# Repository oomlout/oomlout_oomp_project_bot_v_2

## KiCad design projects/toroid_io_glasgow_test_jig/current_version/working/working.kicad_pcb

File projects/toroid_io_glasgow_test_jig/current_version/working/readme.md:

# glasgow
 
## summary 
* id: toroid_io_glasgow_test_jig
* user: toroid_io
* name: glasgow
* board: test_jig
* repo: https://github.com/Toroid-io/glasgow
* src_file_repo_kicad_pcb: hardware/boards/test-jig/test-jig.kicad_pcb
* src_file_repo_kicad_pcb_link: https://github.com/Toroid-io/glasgow/tree/master/hardware/boards/test-jig/test-jig.kicad_pcb

* src_file_repo_sch: hardware/boards/glasgow.sch
* src_file_repo_sch_link: https://github.com/Toroid-io/glasgow/tree/master/hardware/boards/glasgow.sch
* full details link: https://github.com/oomlout/oomlout_oomp_project_bot_v_2/tree/main/projects/toroid_io_glasgow_test_jig/current_version/working

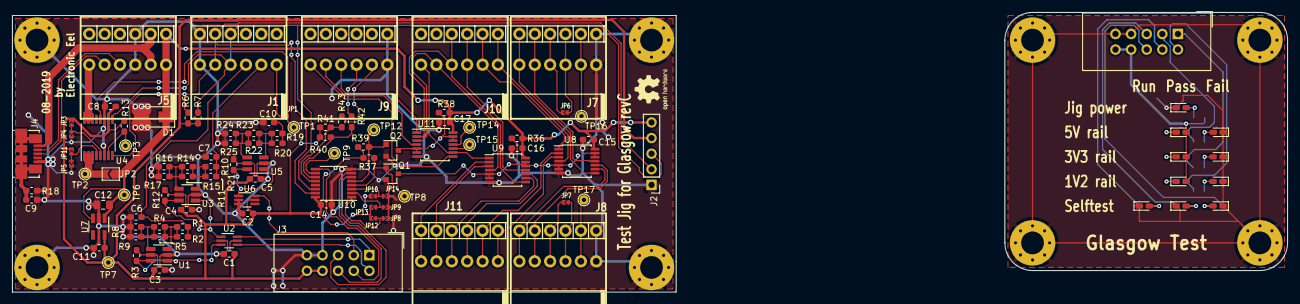
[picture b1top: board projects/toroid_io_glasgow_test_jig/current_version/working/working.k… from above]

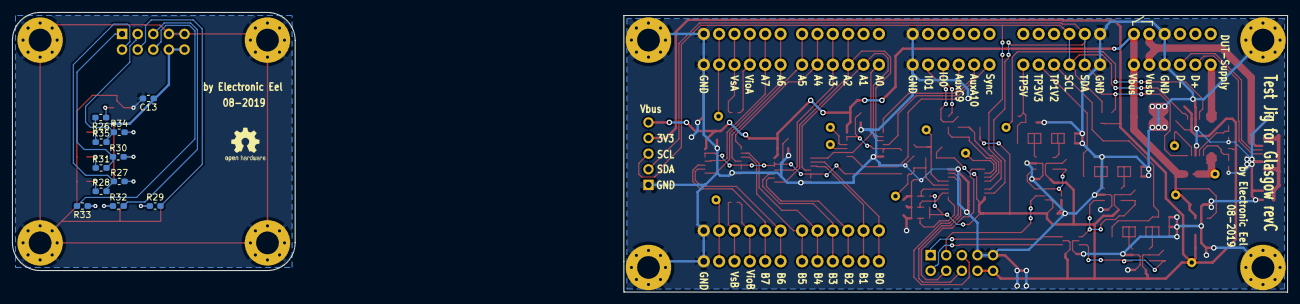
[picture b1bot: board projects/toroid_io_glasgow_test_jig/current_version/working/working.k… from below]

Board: 2 copper layers, 207.5 x 45.5 mm, 129 parts (11 on the bottom side), 90 nets.

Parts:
C1, C2, C3, C4, C5, C6, C7, C8, C9, C10, C13, C14, C15, C16, C17: 100nF; C_0603_1608Metric_Pad1.05x0.95mm_HandSolder
C11: 1µF; C_0603_1608Metric_Pad1.05x0.95mm_HandSolder
C12: 4.7µF; C_0805_2012Metric_Pad1.15x1.40mm_HandSolder
D1: SMAJ5A; D_SMA
D2, D3, D6, D8, D10: green; LED_0603_1608Metric_Castellated
D4, D7, D9, D11: red; LED_0603_1608Metric_Castellated
D5: yellow; LED_0603_1608Metric_Castellated
H1, H2, H3, H4, H5, H6, H7, H8: MountingHole_Pad; MountingHole_3.7mm_Pad_Via
J1, J5, J7, J8, J9, J10, J11: AST04106; TerminalBlock_MetzConnect_AST04106_1x06_Lever_Clamp_45Degree
J2: DNP; PinHeader_1x05_P2.54mm_Vertical
J3, J6: Conn_02x05_Odd_Even; IDC-Header_2x05_P2.54mm_Vertical
J4: USB_B_Micro; USB_Micro-B_Molex_47346-0001
JP1, JP4, JP5, JP6, JP7, JP8, JP9, JP10: SolderJumper_2_Bridged; Solderbridge-small-2pad
JP2: SolderJumper_2_Bridged; SolderJumper-2_P1.3mm_Open_TrianglePad1.0x1.5mm
JP3, JP11, JP12, JP13, JP14: SolderJumper_2_Open; Solderbridge-small-2pad
Q1, Q2: BSS138; SOT-23
R1: 5M1; R_0603_1608Metric_Pad1.05x0.95mm_HandSolder
R2: 68k; R_0603_1608Metric_Pad1.05x0.95mm_HandSolder
R3, R12, R13, R21: 4k7; R_0603_1608Metric_Pad1.05x0.95mm_HandSolder
R4, R8, R16, R22, R24, R40, R41, R42, R43: DNP; R_0603_1608Metric_Pad1.05x0.95mm_HandSolder
R5: 910R; R_0603_1608Metric_Pad1.05x0.95mm_HandSolder
R6, R7: 22k; R_0603_1608Metric_Pad1.05x0.95mm_HandSolder
R9: 33k; R_0603_1608Metric_Pad1.05x0.95mm_HandSolder
R10: 91k; R_0603_1608Metric_Pad1.05x0.95mm_HandSolder
R11: 3M6; R_0603_1608Metric_Pad1.05x0.95mm_HandSolder
R14: 1k; R_0603_1608Metric_Pad1.05x0.95mm_HandSolder
R15: 470R; R_0603_1608Metric_Pad1.05x0.95mm_HandSolder
R17: 12k; R_0603_1608Metric_Pad1.05x0.95mm_HandSolder
R18: 1M; R_0603_1608Metric_Pad1.05x0.95mm_HandSolder
R19: 510k; R_0603_1608Metric_Pad1.05x0.95mm_HandSolder
R20: 110k; R_0603_1608Metric_Pad1.05x0.95mm_HandSolder
R23: 680; R_0603_1608Metric_Pad1.05x0.95mm_HandSolder
R25: 7k5; R_0603_1608Metric_Pad1.05x0.95mm_HandSolder
R26, R27, R28, R29, R30, R31, R32, R33, R34, R35, R36, R38: 2k2; R_0603_1608Metric_Pad1.05x0.95mm_HandSolder
R37, R39: 100K; R_0603_1608Metric_Pad1.05x0.95mm_HandSolder
TP1, TP2, TP3, TP6, TP7, TP8, TP9, TP12, TP14, TP15, TP16, TP17: TestPoint; TestPoint_THTPad_D1.5mm_Drill0.7mm
U1, U3, U5: TPS3700; SOT-23-6_Handsoldering
U2, U6: 74LVC2G14; SOT-363_SC-70-6_Handsoldering
U4: INA260; TSSOP-16_4.4x5mm_P0.65mm
U7: AP2127K-3.3; SOT-23-5_HandSoldering
U8, U9, U11: 74HC4066; TSSOP-14_4.4x5mm_P0.65mm
U10: TCA9534; TSSOP-16_4.4x5mm_P0.65mm

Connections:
+3.3VA: C13.1, D3.2, D6.2, D10.2, J6.8, J6.10, R26.2
+3V3: C1.1, C2.1, C3.1, C4.1, C5.1, C8.1, C11.1, C14.1, J2.4, J3.8, J3.10, JP3.2, JP10.2, JP11.2, JP12.2, JP13.2, R3.1, R6.1, R7.1, R12.1, R13.1, R21.1, R37.1, R39.1, R40.2, R41.2, TP7.1, U1.5, U2.5, U3.5, U4.10, U5.5, U6.5, U7.5, U10.16
/DUT_Supply: J5.6, U4.14, U4.15, U4.16
/LED_1V2: J3.2, U2.4
/LED_3V3: J3.1, U2.6
/LED_5V: J3.3, U6.6
/LED_FAIL: J3.6, U10.7
/LED_PASS: J3.5, U10.6
/LED_RUN: J3.4, U10.9
/SCL: J1.4, J2.3, R7.2, U4.9, U10.14
/SDA: J1.5, J2.2, R6.2, U4.8, U10.15
/TP_1V2: C6.1, J1.3, R1.1, R2.1
/TP_3V3: C7.1, J1.2, R10.1, R11.1
/TP_5V: C10.1, J1.1, JP1.1, R19.1, R20.1
/led-board/LED_1V2: J6.2, R27.1, R28.2
/led-board/LED_3V3: J6.1, R30.1, R31.2
/led-board/LED_5V: J6.3, R34.1, R35.2
/led-board/LED_FAIL: J6.6, R33.2
/led-board/LED_PASS: J6.5, R32.2
/led-board/LED_RUN: J6.4, R29.2
/port-connection/Aux_conn_ctrl_5V: Q2.3, R38.2, U11.5, U11.6, U11.12, U11.13
/port-connection/JIG_GPIO0: J9.3, R42.2
/port-connection/JIG_GPIO1: J9.2, R43.2
/port-connection/Port_conn_ctrl_5V: Q1.3, R36.2, U8.5, U8.6, U8.12, U8.13, U9.5, U9.6, U9.12, U9.13
/port-connection/TP_A0: J10.6, U9.1, U11.9
/port-connection/TP_A1: J10.5, U9.4, U11.3
/port-connection/TP_A2: J10.4, U9.8, U11.2
/port-connection/TP_A3: J10.3, U9.11
/port-connection/TP_A4: J10.2, U8.1
/port-connection/TP_A5: J10.1, U8.4
/port-connection/TP_A6: J7.6, U8.8
/port-connection/TP_A7: J7.5, U8.11
/port-connection/TP_A_Vio: J7.4, JP6.2
/port-connection/TP_A_Vsns: J7.3, JP6.1
/port-connection/TP_Aux_A10: J9.5, U11.4
/port-connection/TP_Aux_C9: J9.4, U11.1
/port-connection/TP_B0: J11.6, U9.2
/port-connection/TP_B1: J11.5, U9.3
/port-connection/TP_B2: J11.4, U9.9
/port-connection/TP_B3: J11.3, U9.10
/port-connection/TP_B4: J11.2, U8.2
/port-connection/TP_B5: J11.1, U8.3
/port-connection/TP_B6: J8.6, U8.9
/port-connection/TP_B7: J8.5, U8.10
/port-connection/TP_B_Vio: J8.4, JP7.2
/port-connection/TP_B_Vsns: J8.3, JP7.1
/port-connection/TP_Sync: J9.6, U11.8
/port-connection/~Aux_conn_ctrl: Q2.1, R39.2, TP12.1, U10.5
/port-connection/~Port_conn_ctrl: Q1.1, R37.2, TP8.1, U10.4
GND: C1.2, C2.2, C3.2, C4.2, C5.2, C6.2, C7.2, C8.2, C9.2, C10.2, C11.2, C12.2, C14.2, C15.2, C16.2, C17.2, D1.2, H1.1, H2.1, H3.1, H4.1, J1.6, J2.1, J3.7, J3.9, J4.5, J5.3, J7.1, J8.1, J9.1, JP4.2, JP5.2, JP8.2, JP9.2, JP14.2, Q1.2, Q2.2, R8.2, R9.2, R16.2, R17.2, R18.2, R24.2, R25.2, U1.2, U2.2, U3.2, U4.6, U4.11, U5.2, U6.2, U6.3, U7.2, U8.7, U9.7, U10.8, U11.7
GNDA: C13.2, D2.1, D4.1, D5.1, D7.1, D8.1, D9.1, D11.1, H5.1, H6.1, H7.1, H8.1, J6.7, J6.9
unnamed: C9.1, J4.6, R18.1
unnamed: D2.2, R26.1
unnamed: D3.1, R27.2
unnamed: D4.2, R28.1
unnamed: D5.2, R29.1
unnamed: D6.1, R30.2
unnamed: D7.2, R31.1
unnamed: D8.2, R32.1
unnamed: D9.2, R33.1
unnamed: D10.1, R34.2
unnamed: D11.2, R35.1
unnamed: J4.1, J5.2
unnamed: J4.2, J5.4
unnamed: J4.3, J5.5
unnamed: J7.2, TP16.1
unnamed: J8.2, TP17.1
unnamed: JP1.2, TP1.1, U4.12
unnamed: JP2.2, TP2.1, U4.1, U4.2, U4.3
unnamed: JP3.1, JP4.1, U4.5
unnamed: JP10.1, JP14.1, U10.3
unnamed: JP5.1, JP11.1, U4.4
unnamed: JP8.1, JP12.1, U10.1
unnamed: JP9.1, JP13.1, U10.2
unnamed: R1.2, R2.2, R4.1, R5.1, U1.3
unnamed: R3.2, U1.1, U1.6, U2.3
unnamed: R4.2, R5.2, R8.1, R9.1, U1.4
unnamed: R10.2, R11.2, R14.1, R15.1, U3.3
unnamed: R12.2, U2.1, U3.1, U3.6
unnamed: R13.2, TP3.1, U4.7
unnamed: R14.2, R15.2, R16.1, R17.1, U3.4
unnamed: R19.2, R20.2, R22.1, R23.1, U5.3
unnamed: R21.2, U5.1, U5.6, U6.1
unnamed: R22.2, R23.2, R24.1, R25.1, U5.4
unnamed: R40.1, R42.1, U10.11
unnamed: R41.1, R43.1, U10.12
unnamed: TP9.1, U10.10
unnamed: TP14.1, U11.11
unnamed: TP15.1, U11.10
VBUS: C12.1, C15.1, C16.1, C17.1, D1.1, J2.5, J5.1, JP2.1, R36.1, R38.1, TP6.1, U7.1, U7.3, U8.14, U9.14, U11.14

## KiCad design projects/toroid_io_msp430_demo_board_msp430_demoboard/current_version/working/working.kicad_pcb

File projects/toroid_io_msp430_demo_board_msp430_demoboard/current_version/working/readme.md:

# msp430_demo_board
 
## summary 
* id: toroid_io_msp430_demo_board_msp430_demoboard
* user: toroid_io
* name: msp430_demo_board
* board: msp430_demoboard
* repo: https://github.com/Toroid-io/msp430_demo_board
* src_file_repo_kicad_pcb: MSP430_DemoBoard.kicad_pcb
* src_file_repo_kicad_pcb_link: https://github.com/Toroid-io/msp430_demo_board/tree/master/MSP430_DemoBoard.kicad_pcb

* src_file_repo_sch: MSP430_DemoBoard.sch
* src_file_repo_sch_link: https://github.com/Toroid-io/msp430_demo_board/tree/master/MSP430_DemoBoard.sch
* full details link: https://github.com/oomlout/oomlout_oomp_project_bot_v_2/tree/main/projects/toroid_io_msp430_demo_board_msp430_demoboard/current_version/working

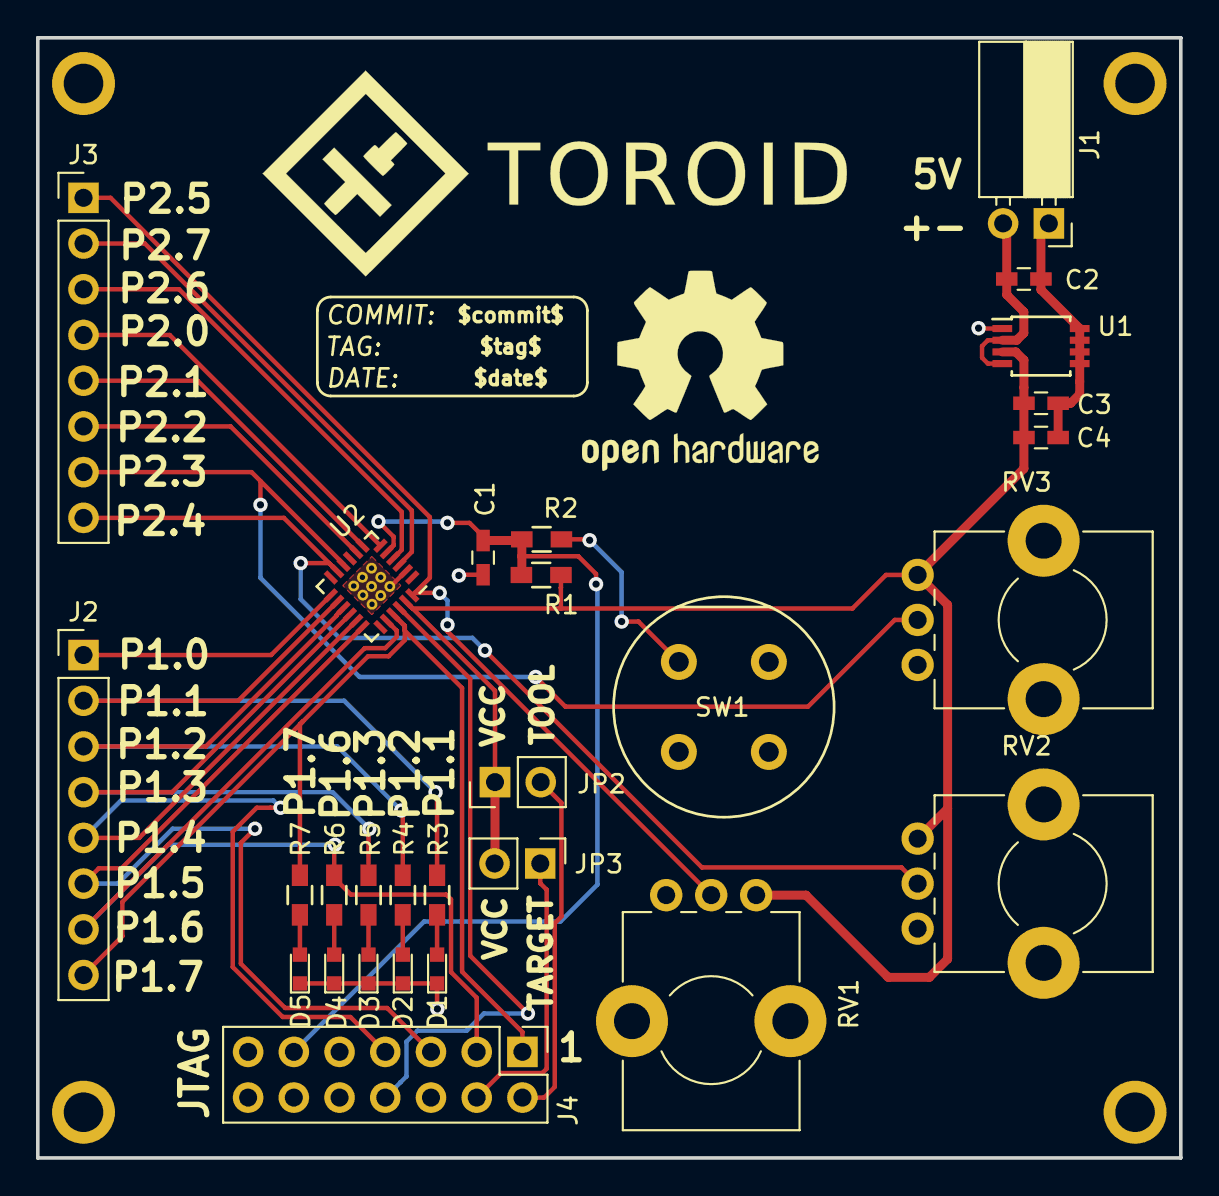
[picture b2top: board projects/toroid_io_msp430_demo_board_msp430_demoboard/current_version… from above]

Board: 2 copper layers, 63.5 x 62.2 mm, 32 parts (0 on the bottom side), 29 nets.

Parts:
C1: 1nF; C_0603_HandSoldering
C2, C3: 100nF; C_0603_HandSoldering
C4: 10uF; C_0603_HandSoldering
D1, D2, D3, D4, D5: LED; LED_0603
J1: VIN; Socket_Strip_Angled_1x02_Pitch2.54mm
J2: P1.X; Pin_Header_Straight_1x08_Pitch2.54mm
J3: P2.X; Pin_Header_Straight_1x08_Pitch2.54mm
J4: JTAG-MSP430; Pin_Header_Straight_2x07_Pitch2.54mm
JP2: VCCTOOL; Pin_Header_Straight_1x02_Pitch2.54mm
JP3: VCCTARGET; Pin_Header_Straight_1x02_Pitch2.54mm
MNT1, MNT2, MNT3, MNT4: MountHole; MountingHole_2.2mm_M2_ISO7380_Pad
R1: 33k; R_0603_HandSoldering
R2, R3, R4, R5, R6, R7: 330; R_0603_HandSoldering
RV1, RV2, RV3: POT; Potentiometer_Bourns_PTV09A-1_Horizontal
SW1: SW_Push_Dual; Push_E-Switch_KS01Q01
U1: ADP1720ARMZ-3.3-R7; TSSOP-8_3x3mm_Pitch0.65mm
U2: MSP430F2101IRGE; QFN-24_4x4mm_Pitch0.5mm_NoMask

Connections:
/P1.0: J2.1, U2.13
/P1.1: J2.2, R3.1, U2.14
/P1.2: J2.3, R4.1, U2.15
/P1.3: J2.4, R5.1, U2.16
/P1.4: J2.5, J4.7, U2.17
/P1.5: J2.6, J4.5, U2.18
/P1.6: J2.7, J4.3, R6.1, U2.20
/P1.7: J2.8, J4.1, R7.1, U2.21
/P2.0: J3.4, U2.6
/P2.1: J3.5, U2.7
/P2.2: J3.6, U2.8
/P2.3: J3.7, RV3.2, U2.10
/P2.4: J3.8, RV2.2, U2.11
/P2.5: J3.1, RV1.2, U2.24
/P2.6: J3.3, U2.4
/P2.7: J3.2, U2.3
/RST: C1.1, J4.11, R1.2, R2.1, U2.5
/TEST: J4.8, U2.22
/VCC: C3.1, C4.1, JP2.1, JP3.2, R1.1, RV1.3, RV2.3, RV3.3, U1.3, U2.23
GND: C1.2, C2.2, C3.2, C4.2, D1.1, D2.1, D3.1, D4.1, D5.1, J1.1, J4.9, RV1.1, RV2.1, RV3.1, SW1.3, U1.1, U1.5, U1.6, U1.7, U1.8, U2.2
unnamed: C2.1, J1.2, U1.2, U1.4
unnamed: D1.2, R3.2
unnamed: D2.2, R4.2
unnamed: D3.2, R5.2
unnamed: D4.2, R6.2
unnamed: D5.2, R7.2
unnamed: J4.2, JP2.2
unnamed: J4.4, JP3.1
unnamed: R2.2, SW1.4

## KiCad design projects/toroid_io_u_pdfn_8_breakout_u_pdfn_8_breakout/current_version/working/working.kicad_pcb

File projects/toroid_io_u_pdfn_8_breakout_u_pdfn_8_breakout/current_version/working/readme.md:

# u_pdfn_8_breakout
 
## summary 
* id: toroid_io_u_pdfn_8_breakout_u_pdfn_8_breakout
* user: toroid_io
* name: u_pdfn_8_breakout
* board: u_pdfn_8_breakout
* repo: https://github.com/Toroid-io/U-PDFN-8_Breakout
* src_file_repo_kicad_pcb: u-pdfn-8_breakout.kicad_pcb
* src_file_repo_kicad_pcb_link: https://github.com/Toroid-io/U-PDFN-8_Breakout/tree/master/u-pdfn-8_breakout.kicad_pcb

* src_file_repo_sch: u-pdfn-8_breakout.sch
* src_file_repo_sch_link: https://github.com/Toroid-io/U-PDFN-8_Breakout/tree/master/u-pdfn-8_breakout.sch
* full details link: https://github.com/oomlout/oomlout_oomp_project_bot_v_2/tree/main/projects/toroid_io_u_pdfn_8_breakout_u_pdfn_8_breakout/current_version/working

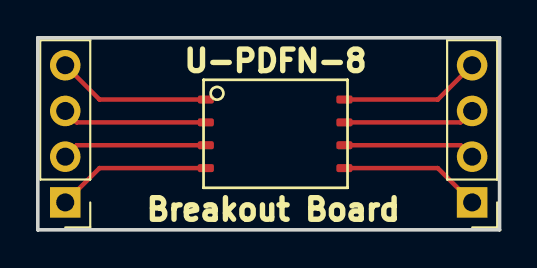
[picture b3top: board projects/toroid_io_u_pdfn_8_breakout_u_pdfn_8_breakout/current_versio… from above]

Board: 2 copper layers, 25.7 x 10.7 mm, 3 parts (0 on the bottom side), 8 nets.

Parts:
J1, J2: CONN_01X04; Pin_Header_Straight_1x04_Pitch2.54mm
U1: MT29F4G01ADAGDWB; U-PDFN-8

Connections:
unnamed: J1.1, U1.4
unnamed: J1.2, U1.3
unnamed: J1.3, U1.2
unnamed: J1.4, U1.1
unnamed: J2.1, U1.5
unnamed: J2.2, U1.6
unnamed: J2.3, U1.7
unnamed: J2.4, U1.8

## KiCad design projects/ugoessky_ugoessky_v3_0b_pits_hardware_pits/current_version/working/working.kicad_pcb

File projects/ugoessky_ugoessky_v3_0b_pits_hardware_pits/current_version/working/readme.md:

# ugoessky_v3_0b_pits_hardware
 
## summary 
* id: ugoessky_ugoessky_v3_0b_pits_hardware_pits
* user: ugoessky
* name: ugoessky_v3_0b_pits_hardware
* board: pits
* repo: https://github.com/UgoesSky/UgoesSky-V3.0b-PITS-Hardware
* src_file_repo_kicad_pcb: PITS/PITS.kicad_pcb
* src_file_repo_kicad_pcb_link: https://github.com/UgoesSky/UgoesSky-V3.0b-PITS-Hardware/tree/master/PITS/PITS.kicad_pcb

* src_file_repo_sch: 
* src_file_repo_sch_link: https://github.com/UgoesSky/UgoesSky-V3.0b-PITS-Hardware/tree/master/
* full details link: https://github.com/oomlout/oomlout_oomp_project_bot_v_2/tree/main/projects/ugoessky_ugoessky_v3_0b_pits_hardware_pits/current_version/working

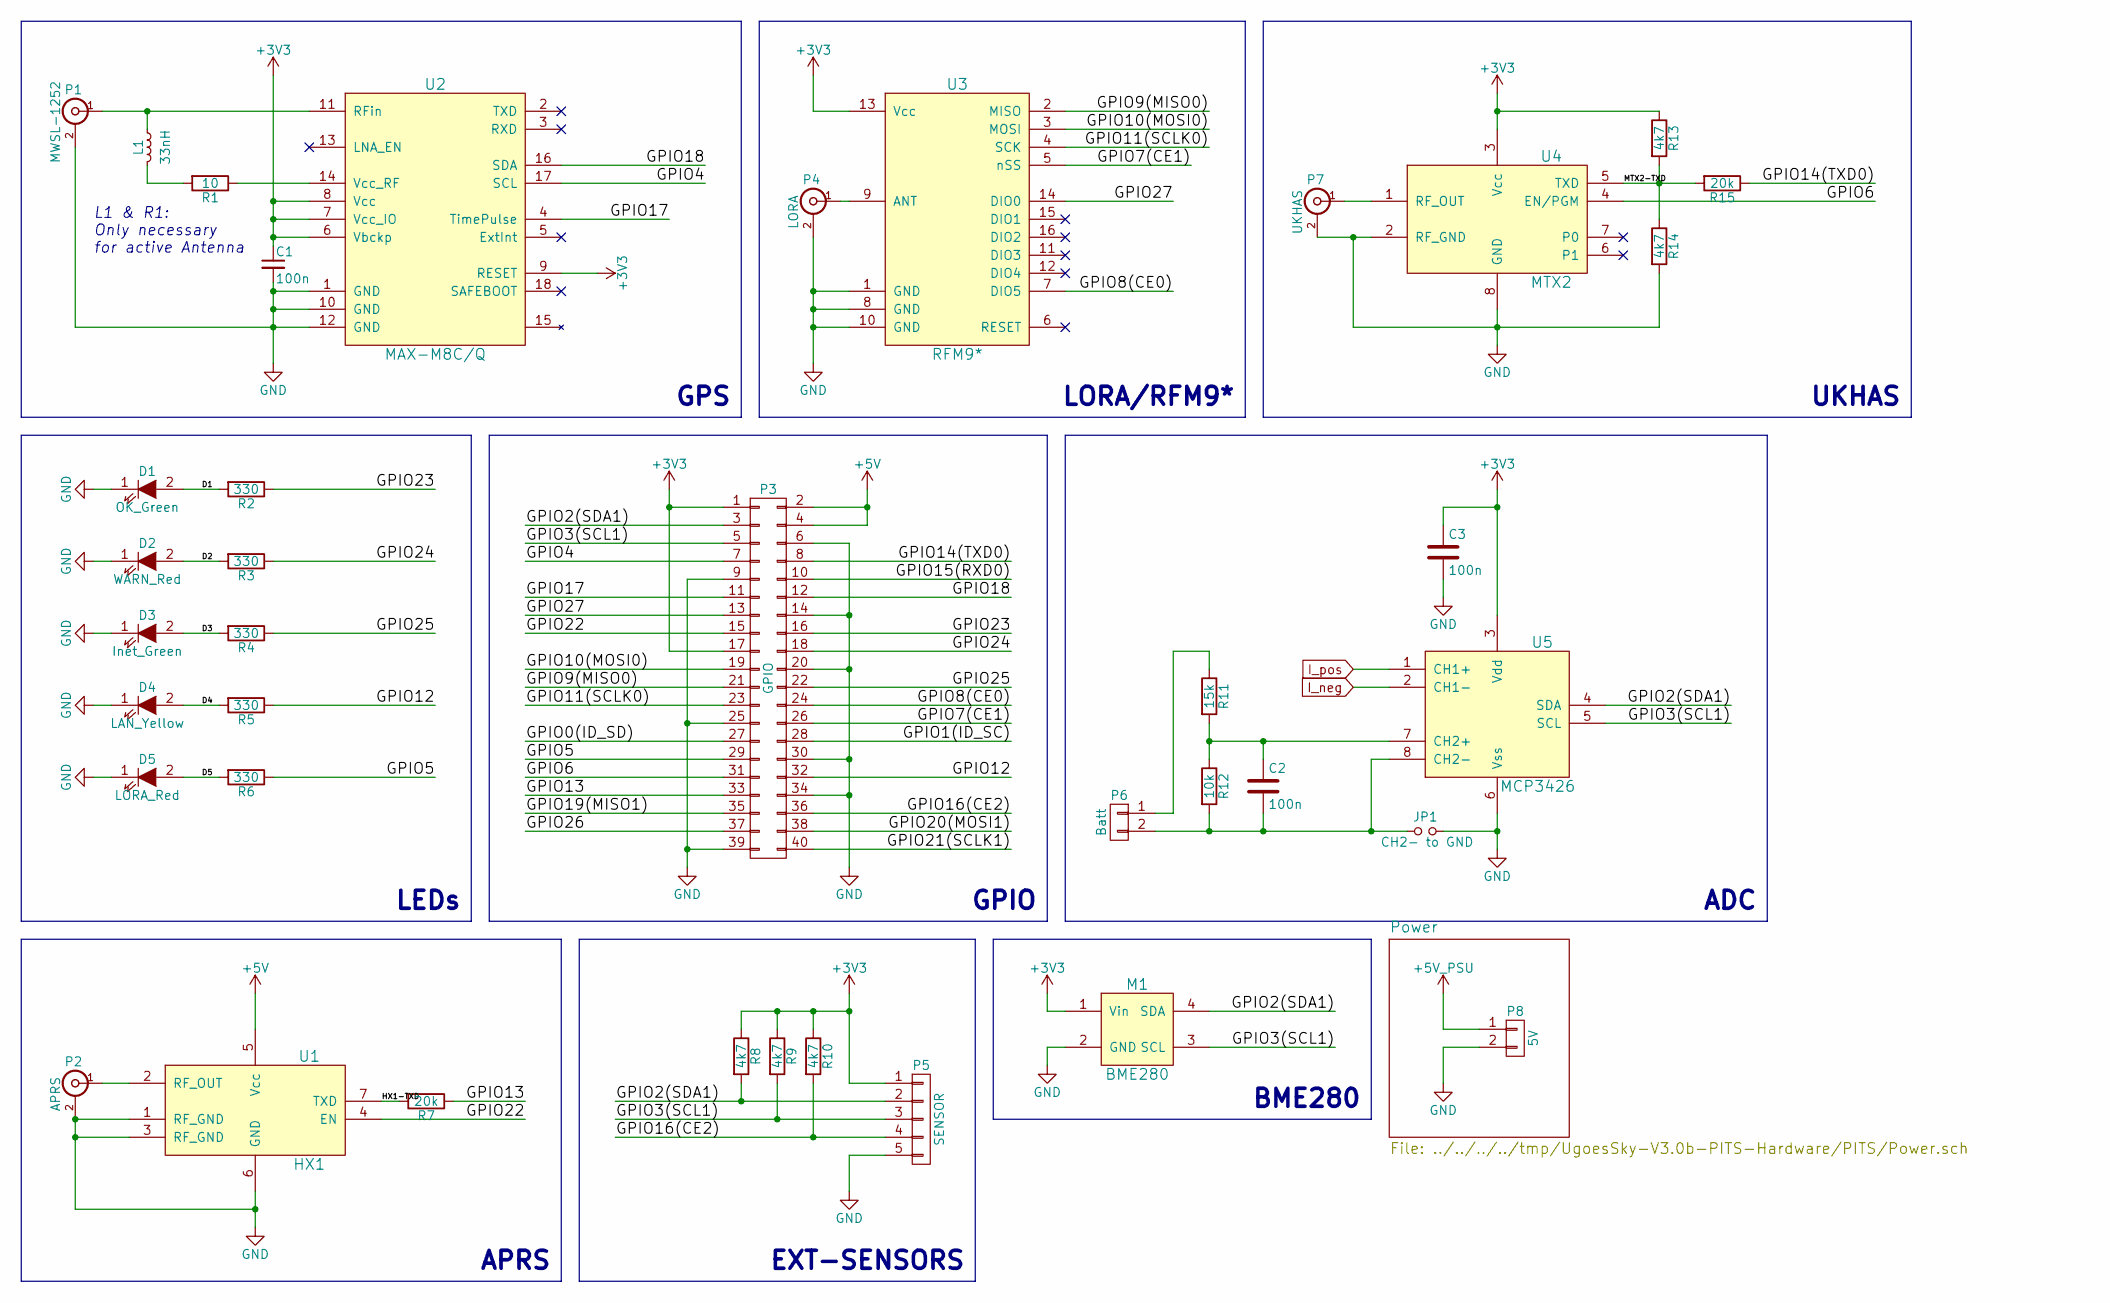
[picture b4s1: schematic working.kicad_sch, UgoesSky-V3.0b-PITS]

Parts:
C1, C2, C3: 100n; C_0603_HandSoldering
D1: OK_Green; LED_0603
D2: WARN_Red; LED_0603
D3: Inet_Green; LED_0603
D4: LAN_Yellow; LED_0603
D5: LORA_Red; LED_0603
JP1: CH2- to GND; R_0603_HandSoldering
L1: 33nH; R_0805_HandSoldering
M1: BME280
P1: MWSL-1252; MWSL1252
P2: APRS; SMA_Edge_small
P3: GPIO; Socket_Strip_Straight_2x20
P4: LORA; SMA_Edge_small
P5: SENSOR; SMD_5_xsmall
P6: Batt; SMD_2_xsmall
P7: UKHAS; SMA_Edge_small
P8: 5V; SMD_2_xsmall
R1: 10; R_0603_HandSoldering
R2, R3, R4, R5, R6: 330; R_0603_HandSoldering
R7, R15: 20k; R_0603_HandSoldering
R8, R9, R10, R13, R14: 4k7; R_0603_HandSoldering
R11: 15k; R_0805_HandSoldering
R12: 10k; R_0805_HandSoldering
U1: HX1; HX1_Horizontal
U2: MAX-M8C/Q; MAX-M8
U3: RFM9*; RFM9xW
U4: MTX2
U5: MCP3426; SOIC-8_3.9x4.9mm_Pitch1.27mm

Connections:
+3V3: C1.1, C3.1, M1.1 (Vin), P3.1, P3.17, P5.1, R8.1, R9.1, R10.1, R13.1, U2.6 (Vbckp), U2.7 (Vcc_IO), U2.8 (Vcc), U2.9 (RESET), U3.13 (Vcc), U4.3 (Vcc), U5.3 (Vdd)
/D1: D1.2 (A), R2.2
/D2: D2.2 (A), R3.2
/D3: D3.2 (A), R4.2
/D4: D4.2 (A), R5.2
/D5: D5.2 (A), R6.2
/GPIO0(ID_SD): P3.27
/GPIO1(ID_SC): P3.28
/GPIO2(SDA1): M1.4 (SDA), P3.3, P5.2, R8.2, U5.4 (SDA)
/GPIO3(SCL1): M1.3 (SCL), P3.5, P5.3, R9.2, U5.5 (SCL)
/GPIO4: P3.7, U2.17 (SCL)
/GPIO5: P3.29, R6.1
/GPIO6: P3.31, U4.4 (EN/PGM)
/GPIO7(CE1): P3.26, U3.5 (nSS)
/GPIO8(CE0): P3.24, U3.7 (DIO5)
/GPIO9(MISO0): P3.21, U3.2 (MISO)
/GPIO10(MOSI0): P3.19, U3.3 (MOSI)
/GPIO11(SCLK0): P3.23, U3.4 (SCK)
/GPIO12: P3.32, R5.1
/GPIO13: P3.33, R7.1
/GPIO14(TXD0): P3.8, R15.1
/GPIO15(RXD0): P3.10
/GPIO16(CE2): P3.36, P5.4, R10.2
/GPIO17: P3.11, U2.4 (TimePulse)
/GPIO18: P3.12, U2.16 (SDA)
/GPIO19(MISO1): P3.35
/GPIO20(MOSI1): P3.38
/GPIO21(SCLK1): P3.40
/GPIO22: P3.15, U1.4 (EN)
/GPIO23: P3.16, R2.1
/GPIO24: P3.18, R3.1
/GPIO25: P3.22, R4.1
/GPIO26: P3.37
/GPIO27: P3.13, U3.14 (DIO0)
/HX1-TXD: R7.2, U1.7 (TXD)
/MTX2-TXD: R13.2, R14.1, R15.2, U4.5 (TXD)
GND: C1.2, C3.2, D1.1 (K), D2.1 (K), D3.1 (K), D4.1 (K), D5.1 (K), JP1.2, M1.2 (GND), P1.2 (Ext), P2.2 (Ext), P3.6, P3.9, P3.14, P3.20, P3.25, P3.30, P3.34, P3.39, P4.2 (Ext), P5.5, P7.2 (Ext), P8.2, R14.2, U1.1 (RF_GND), U1.3 (RF_GND), U1.6 (GND), U2.1 (GND), U2.10 (GND), U2.12 (GND), U3.1 (GND), U3.8 (GND), U3.10 (GND), U4.2 (RF_GND), U4.8 (GND), U5.6 (Vss); also elsewhere on the board
unnamed: C2.1, R11.2, R12.1, U5.7 (CH2+)
unnamed: C2.2, JP1.1, P6.2, R12.2, U5.8 (CH2-)
unnamed: L1.1, P1.1 (In), U2.11 (RFin)
unnamed: L1.2, R1.2
unnamed: P2.1 (In), U1.2 (RF_OUT)
unnamed: P4.1 (In), U3.9 (ANT)
unnamed: P6.1, R11.1
unnamed: P7.1 (In), U4.1 (RF_OUT)
unnamed: R1.1, U2.14 (Vcc_RF)

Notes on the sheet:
LORA/RFM9*
UKHAS
EXT-SENSORS
BME280
GPIO
GPS
L1 & R1: Only necessary for active Antenna
ADC
LEDs
APRS

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
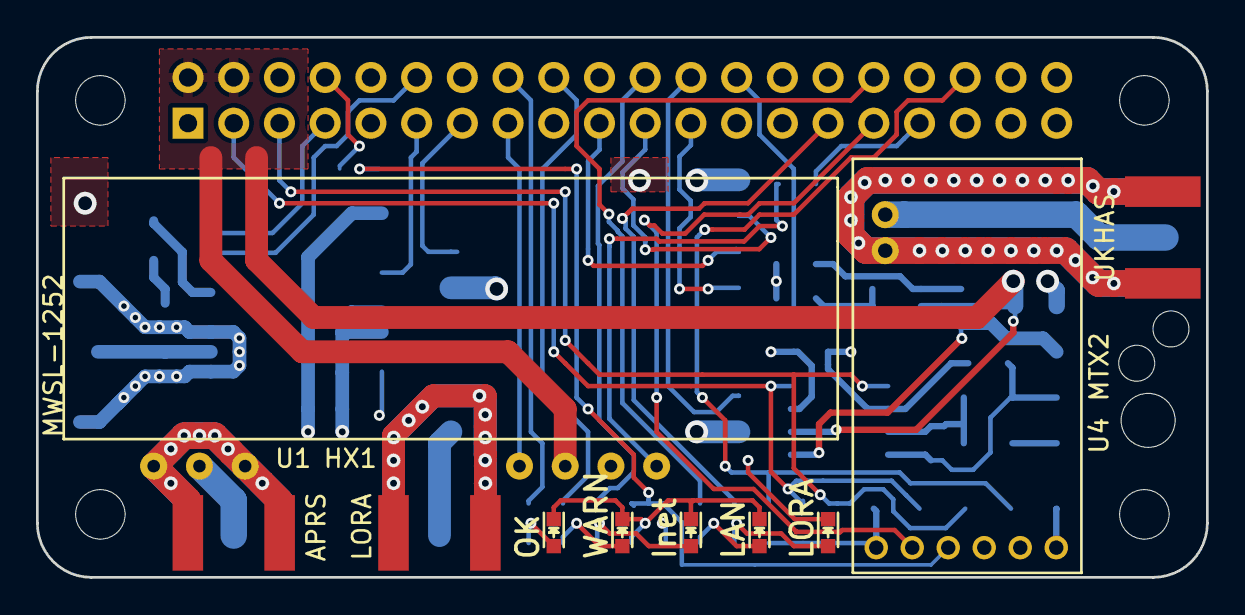
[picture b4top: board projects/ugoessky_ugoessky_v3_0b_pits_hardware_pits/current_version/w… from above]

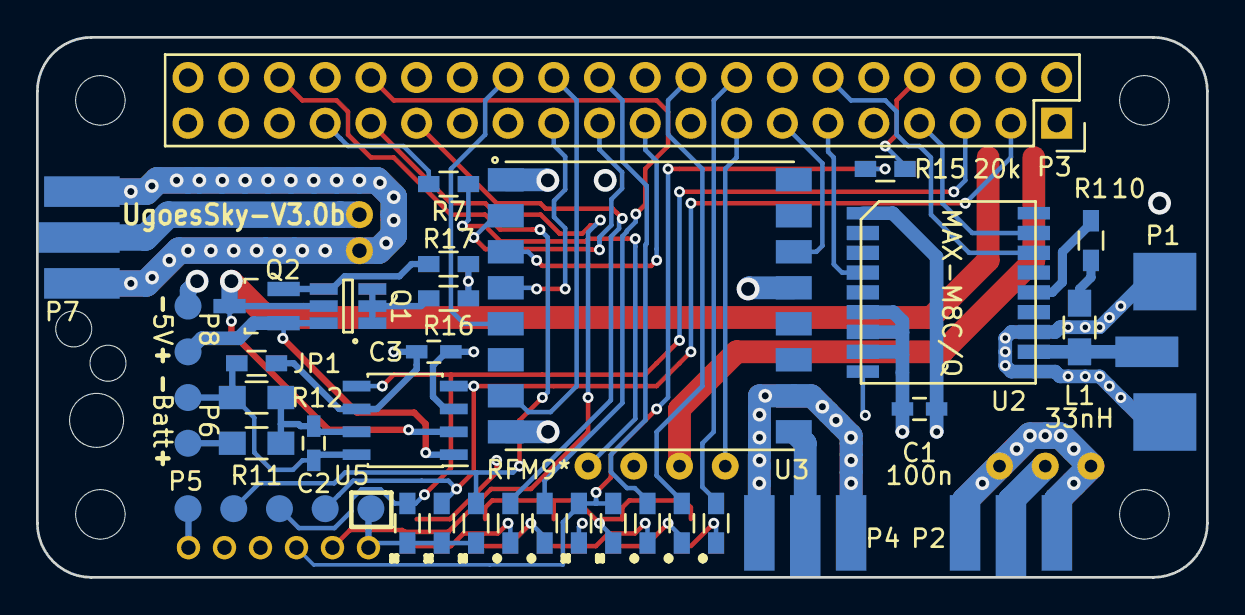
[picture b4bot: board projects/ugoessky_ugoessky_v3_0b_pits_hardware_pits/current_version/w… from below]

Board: 4 copper layers, 65.0 x 30.0 mm, 42 parts (35 on the bottom side), 43 nets.

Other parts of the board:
Q1: DMMT5401; SOT-23-6_Handsoldering
Q2: DMP1045U; SOT-23_Handsoldering
R16: 10k; R_0603_HandSoldering
R17: 47k; R_0603_HandSoldering

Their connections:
GND: R16.2, R17.2; also elsewhere on the board
unnamed: Q1.1, Q1.2, Q1.3, R16.1
unnamed: Q1.4, Q2.2, R17.1

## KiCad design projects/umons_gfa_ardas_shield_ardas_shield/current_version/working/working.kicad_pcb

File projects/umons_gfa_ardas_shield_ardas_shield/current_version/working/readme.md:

# ardas_shield
 
## summary 
* id: umons_gfa_ardas_shield_ardas_shield
* user: umons_gfa
* name: ardas_shield
* board: ardas_shield
* repo: https://github.com/UMONS-GFA/ardas-shield
* src_file_repo_kicad_pcb: ardas_shield.kicad_pcb
* src_file_repo_kicad_pcb_link: https://github.com/UMONS-GFA/ardas-shield/tree/master/ardas_shield.kicad_pcb

* src_file_repo_sch: ardas_shield.sch
* src_file_repo_sch_link: https://github.com/UMONS-GFA/ardas-shield/tree/master/ardas_shield.sch
* full details link: https://github.com/oomlout/oomlout_oomp_project_bot_v_2/tree/main/projects/umons_gfa_ardas_shield_ardas_shield/current_version/working

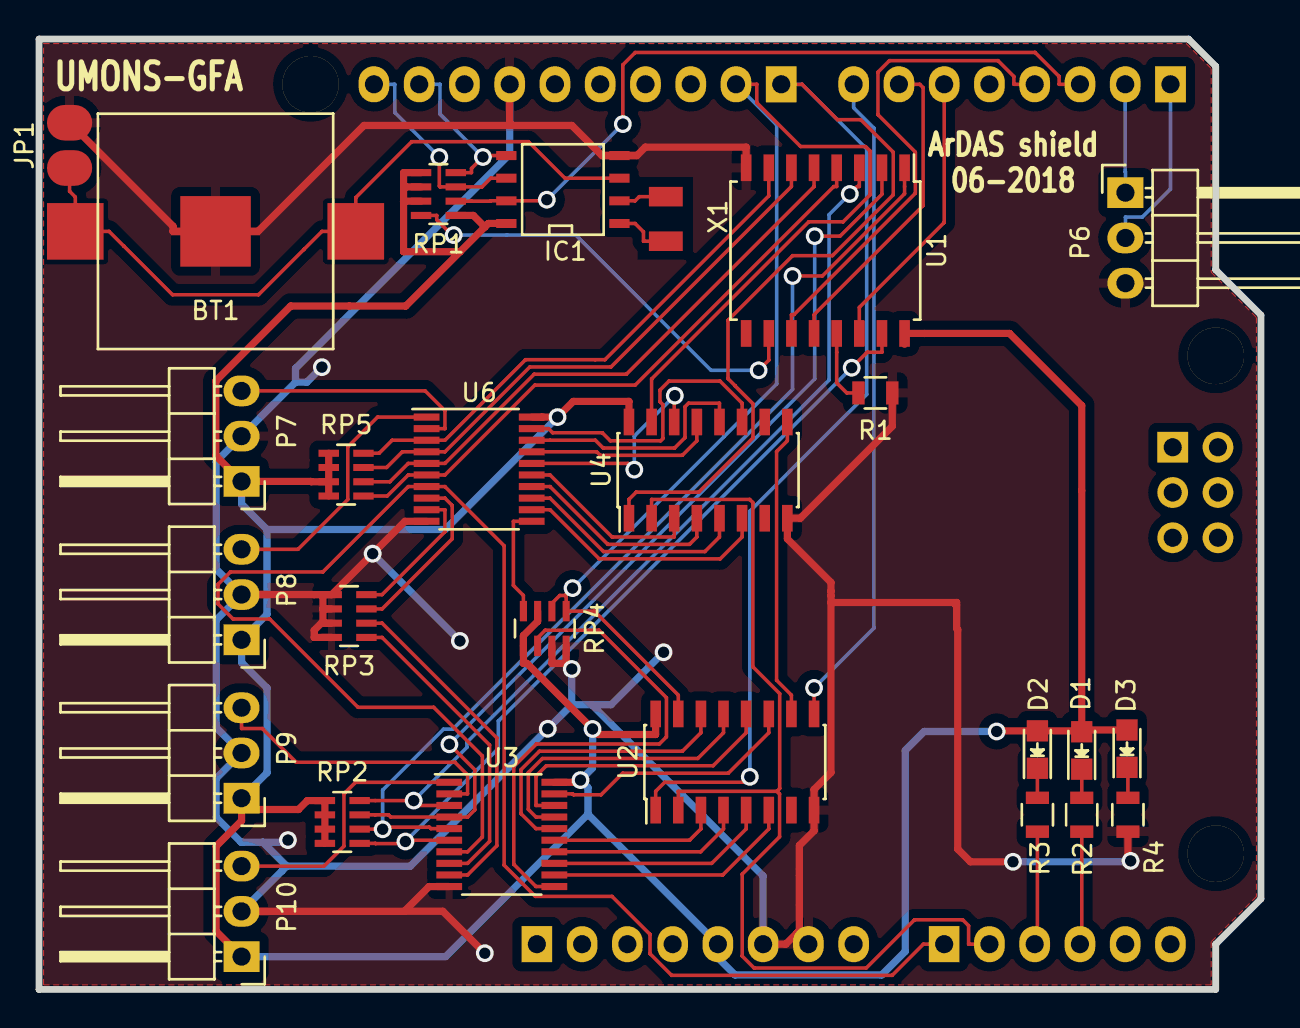
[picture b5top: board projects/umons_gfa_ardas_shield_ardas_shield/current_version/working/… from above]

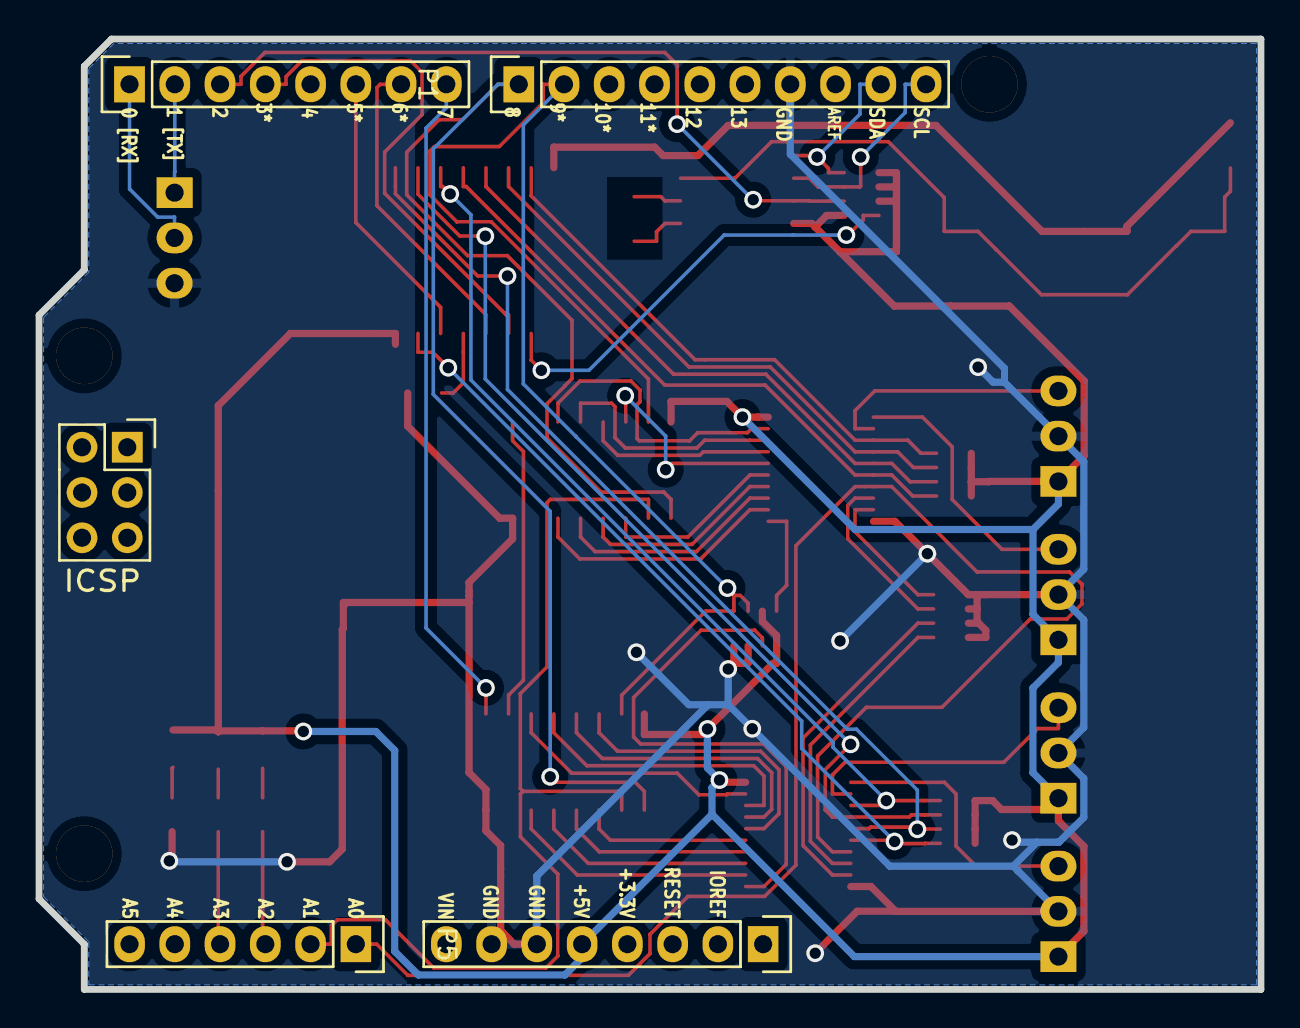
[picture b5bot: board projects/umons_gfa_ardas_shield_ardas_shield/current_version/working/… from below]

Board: 2 copper layers, 68.6 x 53.3 mm, 34 parts (5 on the bottom side), 60 nets.

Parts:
BT1: Battery; BATTERY_KEYSTONE_12mm
D1: LED Green; LED-0805
D2: LED Yellow; LED-0805
D3: LED Red; LED-0805
IC1: DS1307; SOIC-8-N
JP1: Jumper_NO_Small; small_no_jumper
P1: CONN_10; Pin_Header_Straight_1x10
P2, P3: CONN_8; Pin_Header_Straight_1x08
P4: CONN_ICSP; Socket_Strip_Straight_2x03
P5: CONN_6; Pin_Header_Straight_1x06
P6: TTL_COMM; Pin_Header_Angled_1x03
P7, P8, P9, P10: CONN_01X03; Pin_Header_Angled_1x03
R1: 10k; R_0805
R2, R3: 150 Ohm; R_0805
R4: 160 Ohm; R_0805
RP1: R_4x4.7k; R_Array_Convex_4x0603
RP2, RP3, RP4, RP5: R_4x10k; R_Array_Convex_4x0603
U1: 74HC595; SOIC-16_7.5x10.3mm_Pitch1.27mm
U2, U4: 74HC165; SOIC-16_3.9x9.9mm_Pitch1.27mm
U3, U6: SN74LV8154; TSSOP-20_4.4x6.5mm_Pitch0.65mm
V4, V5, V6: MountingHole_125mil
X1: CRYSTAL; XTAL_ABRACON_ABS07

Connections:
+5V: D1.2, D2.2, D3.2, IC1.8, P2.5, P7.1, P8.1, P9.1, P10.1, RP1.1, RP1.5, RP1.6, RP1.7, RP2.1, RP2.2, RP2.3, RP2.4, RP4.3, RP4.5, RP5.1, RP5.2, RP5.3, RP5.4, U1.16, U2.16, U3.20, U4.16, U6.20
A04: IC1.5, P1.9, RP1.4
A05: IC1.6, P1.10, RP1.3
CH1: P10.3, U3.1
CH2: P9.3, U3.2
CH3: P8.3, U6.1
CH4: P7.3, U6.2
D00: P3.1, P6.2
D01: P3.2, P6.1
D02: IC1.7, P3.3, RP1.2
D03: P3.4, U1.11
D05: P3.6, U1.14
D06: P3.7, U1.12
D07: P3.8, U2.9
D08: P1.1, U2.1, U4.1
D09: P1.2, RP4.1, RP4.2, U2.15, U4.15
D14: P5.1, U3.7, U6.7
D15: P5.2, U2.2, U4.2
D16: P5.3, R3.2
D17: P5.4, R2.2
GND: BT1.2, IC1.4, JP1.1, P1.7, P2.6, P2.7, P6.3, P7.2, P8.2, P9.2, P10.2, R1.1, R4.2, RP3.5, RP3.6, RP3.7, RP3.8, RP4.7, RP4.8, U1.8, U2.8, U3.10, U4.8, U6.10
unnamed: BT1.1, IC1.3, JP1.2
unnamed: D1.1, R2.1
unnamed: D2.1, R3.1
unnamed: D3.1, R4.1
unnamed: IC1.1, X1.1
unnamed: IC1.2, X1.2
unnamed: R1.2, U1.13
unnamed: RP1.8, U1.10
unnamed: RP2.5, U1.15, U3.6
unnamed: RP2.6, U1.1, U3.5
unnamed: RP2.7, U1.2, U3.4
unnamed: RP2.8, U1.3, U3.3
unnamed: RP3.1, U3.8
unnamed: RP3.2, U3.9
unnamed: RP3.3, U6.8
unnamed: RP3.4, U6.9
unnamed: RP4.4, U6.11
unnamed: RP4.6, U3.11
unnamed: RP5.5, U1.4, U6.6
unnamed: RP5.6, U1.5, U6.5
unnamed: RP5.7, U1.6, U6.4
unnamed: RP5.8, U1.7, U6.3
unnamed: U2.3, U3.15
unnamed: U2.4, U3.14
unnamed: U2.5, U3.13
unnamed: U2.6, U3.12
unnamed: U2.10, U4.9
unnamed: U2.11, U3.19
unnamed: U2.12, U3.18
unnamed: U2.13, U3.17
unnamed: U2.14, U3.16
unnamed: U4.3, U6.15
unnamed: U4.4, U6.14
unnamed: U4.5, U6.13
unnamed: U4.6, U6.12
unnamed: U4.11, U6.19
unnamed: U4.12, U6.18
unnamed: U4.13, U6.17
unnamed: U4.14, U6.16

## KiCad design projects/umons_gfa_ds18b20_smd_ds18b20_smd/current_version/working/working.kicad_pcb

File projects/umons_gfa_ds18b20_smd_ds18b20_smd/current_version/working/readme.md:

# ds18b20_smd
 
## summary 
* id: umons_gfa_ds18b20_smd_ds18b20_smd
* user: umons_gfa
* name: ds18b20_smd
* board: ds18b20_smd
* repo: https://github.com/UMONS-GFA/ds18b20-smd
* src_file_repo_kicad_pcb: ds18b20-smd.kicad_pcb
* src_file_repo_kicad_pcb_link: https://github.com/UMONS-GFA/ds18b20-smd/tree/master/ds18b20-smd.kicad_pcb

* src_file_repo_sch: ds18b20-smd.sch
* src_file_repo_sch_link: https://github.com/UMONS-GFA/ds18b20-smd/tree/master/ds18b20-smd.sch
* full details link: https://github.com/oomlout/oomlout_oomp_project_bot_v_2/tree/main/projects/umons_gfa_ds18b20_smd_ds18b20_smd/current_version/working

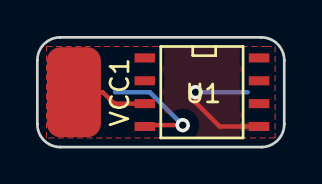
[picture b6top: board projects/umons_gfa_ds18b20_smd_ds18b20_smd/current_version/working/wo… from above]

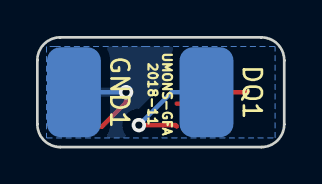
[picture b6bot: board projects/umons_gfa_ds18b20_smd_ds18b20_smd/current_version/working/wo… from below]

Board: 2 copper layers, 13.7 x 6.1 mm, 4 parts (2 on the bottom side), 3 nets.

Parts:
DQ1: Pad; PAD3mmx5mm
GND1: Pad; PAD3mmx5mm
U1: DS18B20Z; SOIC-8-N
VCC1: Pad; PAD3mmx5mm

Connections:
DQ: DQ1.1, U1.4
GND: GND1.1, U1.5
VCC: U1.3, VCC1.1
